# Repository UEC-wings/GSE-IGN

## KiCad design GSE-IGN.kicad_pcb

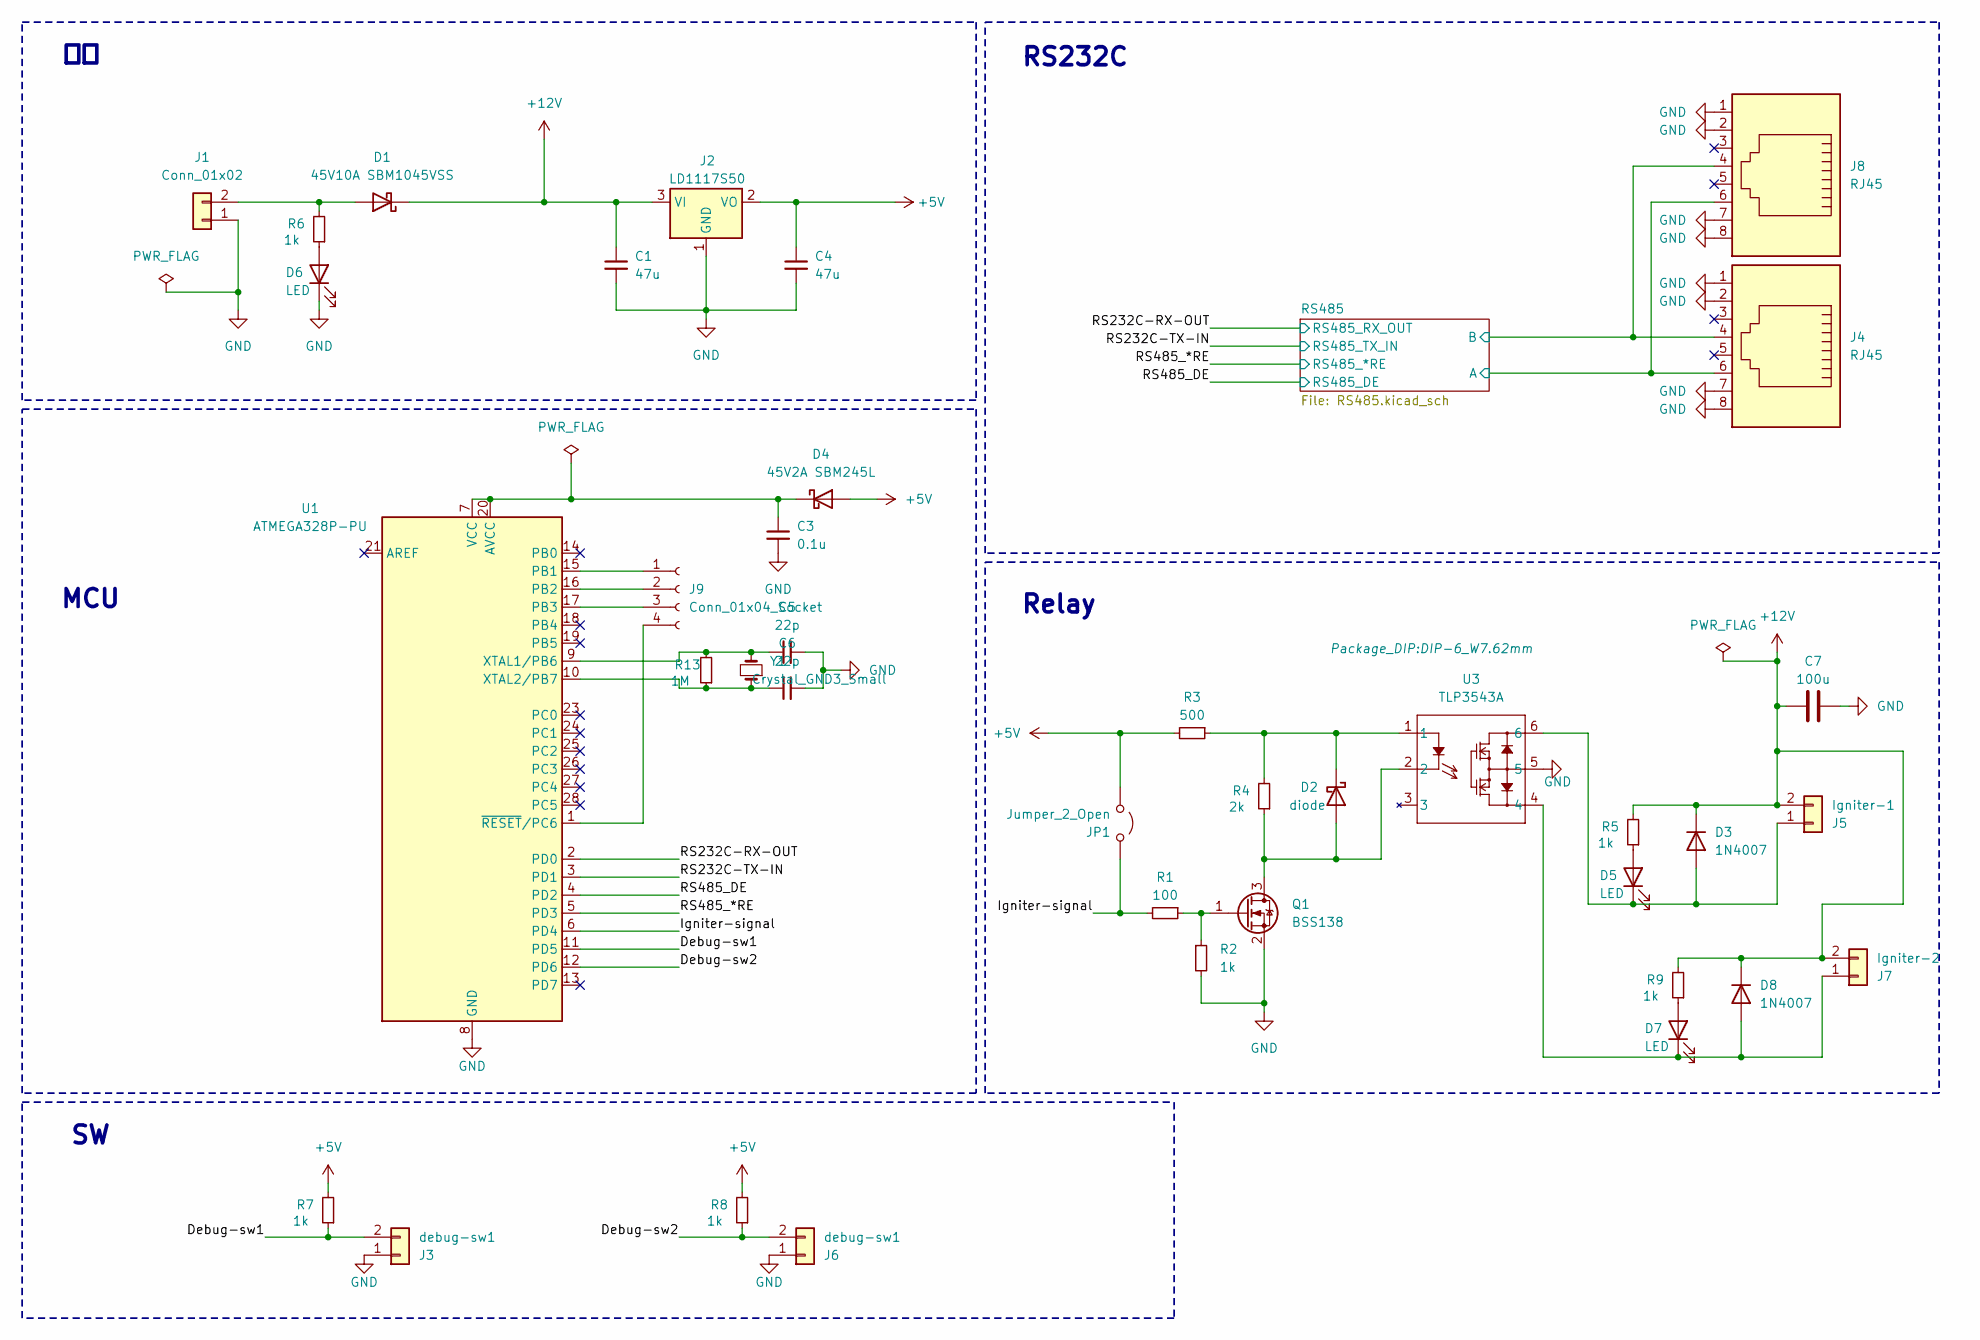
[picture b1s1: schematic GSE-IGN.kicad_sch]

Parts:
C1, C4: 47u; CP_Radial_D4.0mm_P1.50mm
C3: 0.1u; C_0603_1608Metric_Pad1.08x0.95mm_HandSolder
C5, C6: 22p; C_0603_1608Metric
C7: 100u; CP_Radial_D5.0mm_P2.00mm
D1: 45V10A SBM1045VSS; SBM1060LSS_P20mm_Horizontal
D2: diode; D_DO-41_SOD81_P10.16mm_Horizontal
D3, D8: 1N4007; D_DO-41_SOD81_P10.16mm_Horizontal
D4: 45V2A SBM245L; D_DO-41_SOD81_P10.16mm_Horizontal
D5, D6, D7: LED; LED_D3.0mm
J1: Conn_01x02; AMASS_XT60-M_1x02_P7.20mm_Vertical
J2: LD1117S50; SOT-223-3_TabPin2
J3, J6: debug-sw1; JST_XH_B2B-XH-A_1x02_P2.50mm_Vertical
J4, J8: RJ45; 78108P8C
J5: Igniter-1; AMASS_XT60-M_1x02_P7.20mm_Vertical
J7: Igniter-2; AMASS_XT60-M_1x02_P7.20mm_Vertical
J9: Conn_01x04_Socket; PinSocket_1x04_P2.54mm_Vertical
JP1: Jumper_2_Open; JST_XH_B2B-XH-A_1x02_P2.50mm_Vertical
Q1: BSS138; SOT-23
R1: 100; R_Axial_DIN0207_L6.3mm_D2.5mm_P7.62mm_Horizontal
R2, R5, R6, R7, R8, R9: 1k; R_Axial_DIN0207_L6.3mm_D2.5mm_P7.62mm_Horizontal
R3: 500; R_Axial_DIN0207_L6.3mm_D2.5mm_P7.62mm_Horizontal
R4: 2k; R_Axial_DIN0207_L6.3mm_D2.5mm_P7.62mm_Horizontal
R13: 1M; R_Axial_DIN0207_L6.3mm_D2.5mm_P7.62mm_Horizontal
U1: ATMEGA328P-PU; DIP-28_W7.62mm
U3: TLP3543A; DIP-6_W7.62mm
Y1: Crystal_GND3_Small; Crystal_HC49-4H_Vertical

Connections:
+5V: C4.1, D4.2 (A), J2.2 (VO), JP1.1 (A), R3.2, R7.2, R8.2; also elsewhere on the board
+12V: C1.1, C7.1, D1.1 (K), D3.1 (K), D8.1 (K), J2.3 (VI), J5.2, J7.2, R5.2, R9.2
/Debug-sw1: J3.2, R7.1, U1.11 (PD5)
/Debug-sw2: J6.2, R8.1, U1.12 (PD6)
/Igniter-signal: JP1.2 (B), R1.2, U1.6 (PD4)
/RS232C-RX-OUT: U1.2 (PD0); also elsewhere on the board
/RS232C-TX-IN: U1.3 (PD1); also elsewhere on the board
/RS485/A: J4.6, J8.6; also elsewhere on the board
/RS485/B: J4.4, J8.4; also elsewhere on the board
/RS485_*RE: U1.5 (PD3); also elsewhere on the board
/RS485_DE: U1.4 (PD2); also elsewhere on the board
GND: C1.2, C3.2, C4.2, C5.2, C6.2, C7.2, D6.1 (K), J1.1, J2.1 (GND), J3.1, J4.1, J4.2, J4.7, J4.8, J6.1, J8.1, J8.2, J8.7, J8.8, J8.9, J8.10, Q1.2 (S), R2.2, U1.8 (GND), U1.22 (GND), U3.5; also elsewhere on the board
unnamed: D1.2 (A), J1.2, R6.2
unnamed: D2.2 (A), Q1.3 (D), R4.1, U3.2
unnamed: D2.1 (K), R3.1, R4.2, U3.1
unnamed: D3.2 (A), D5.1 (K), J5.1, U3.6
unnamed: C3.1, D4.1 (K), U1.7 (VCC), U1.20 (AVCC)
unnamed: D5.2 (A), R5.1
unnamed: D6.2 (A), R6.1
unnamed: D7.2 (A), R9.1
unnamed: D7.1 (K), D8.2 (A), J7.1, U3.4
unnamed: J9.1, U1.15 (PB1)
unnamed: J9.2, U1.16 (PB2)
unnamed: J9.3, U1.17 (PB3)
unnamed: J9.4, U1.1 (~RESET/PC6)
unnamed: Q1.1 (G), R1.1, R2.1
unnamed: C5.1, R13.2, U1.9 (XTAL1/PB6), Y1.2
unnamed: C6.1, R13.1, U1.10 (XTAL2/PB7), Y1.1

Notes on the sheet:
MCU
Relay
RS232C

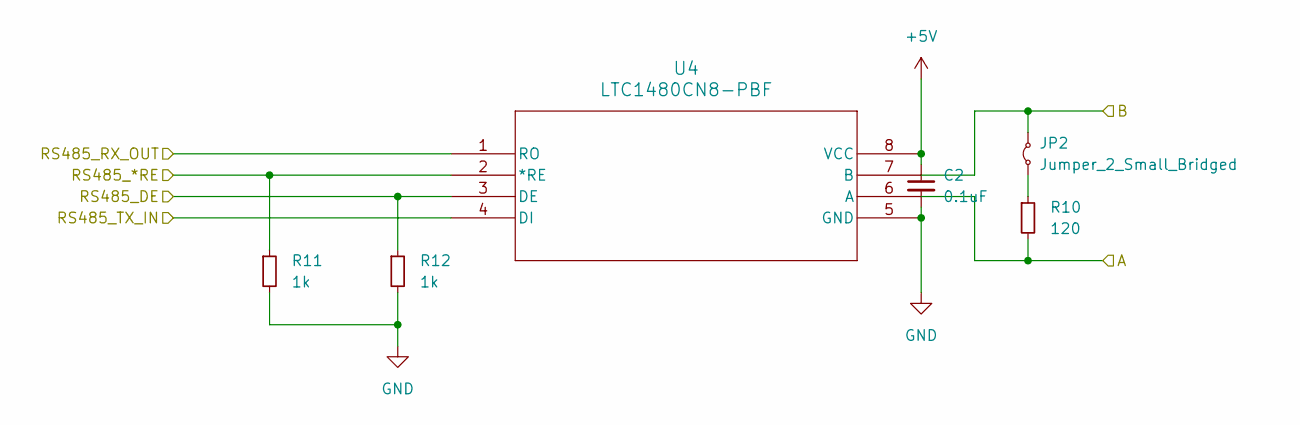
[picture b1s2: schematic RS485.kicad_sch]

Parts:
C2: 0.1uF; C_0603_1608Metric_Pad1.08x0.95mm_HandSolder
JP2: Jumper_2_Small_Bridged; JST_XH_B2B-XH-A_1x02_P2.50mm_Vertical
R10: 120; R_Axial_DIN0207_L6.3mm_D2.5mm_P7.62mm_Horizontal
R11, R12: 1k; R_Axial_DIN0207_L6.3mm_D2.5mm_P7.62mm_Horizontal
U4: LTC1480CN8-PBF; PDIP-8_N_LIT

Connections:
+5V: C2.1, U4.8 (VCC); also elsewhere on the board
/RS232C-RX-OUT: U4.1 (RO); also elsewhere on the board
/RS232C-TX-IN: U4.4 (DI); also elsewhere on the board
/RS485/A: R10.2, U4.6 (A); also elsewhere on the board
/RS485/B: JP2.2 (B), U4.7 (B); also elsewhere on the board
/RS485_*RE: R11.1, U4.2 (*RE); also elsewhere on the board
/RS485_DE: R12.1, U4.3 (DE); also elsewhere on the board
GND: C2.2, R11.2, R12.2, U4.5 (GND); also elsewhere on the board
unnamed: JP2.1 (A), R10.1

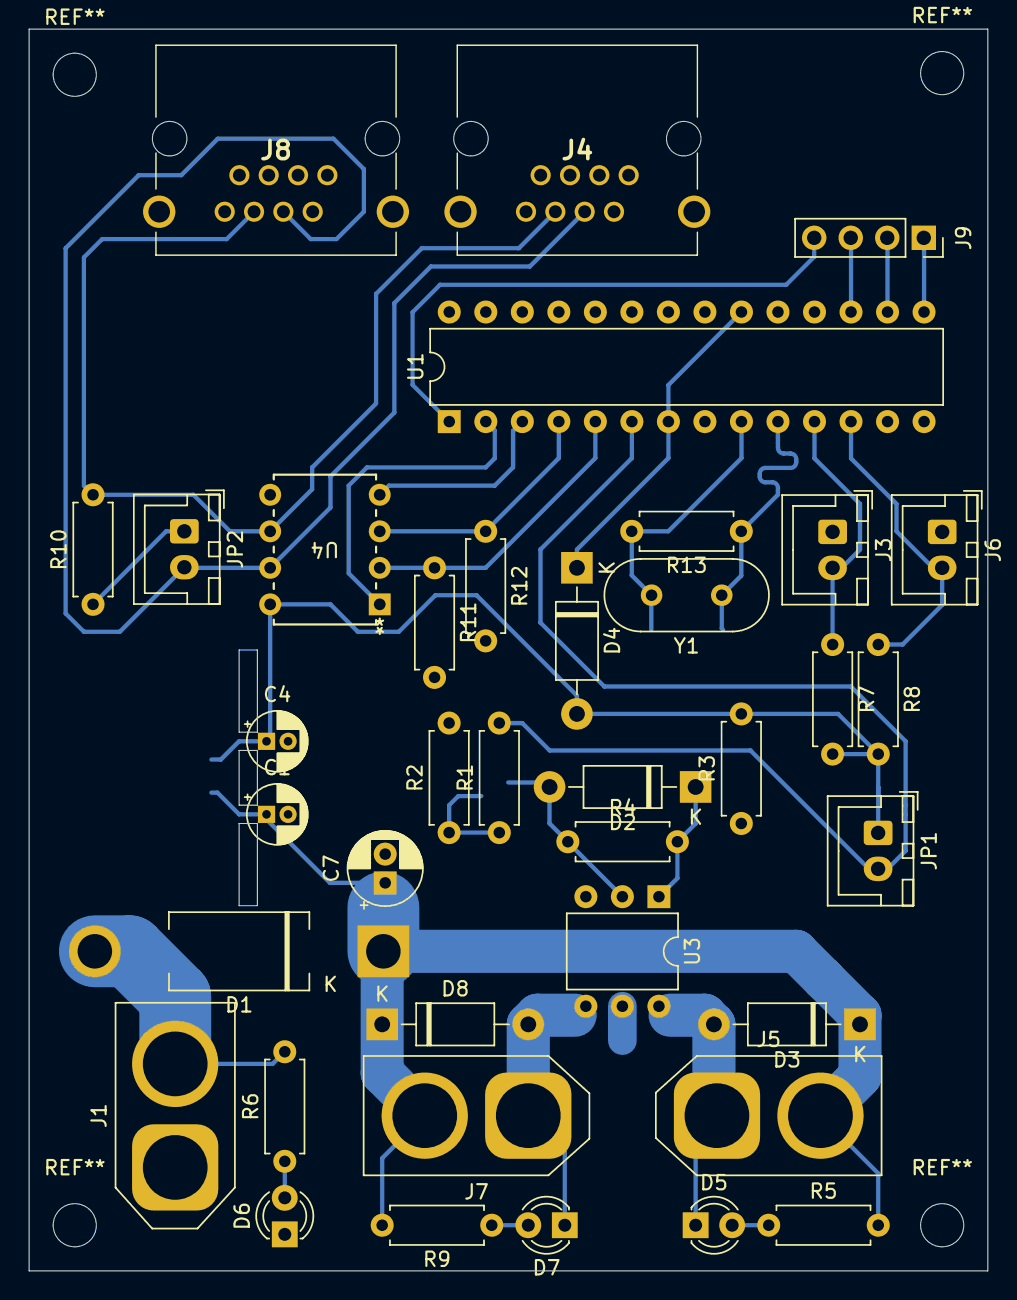
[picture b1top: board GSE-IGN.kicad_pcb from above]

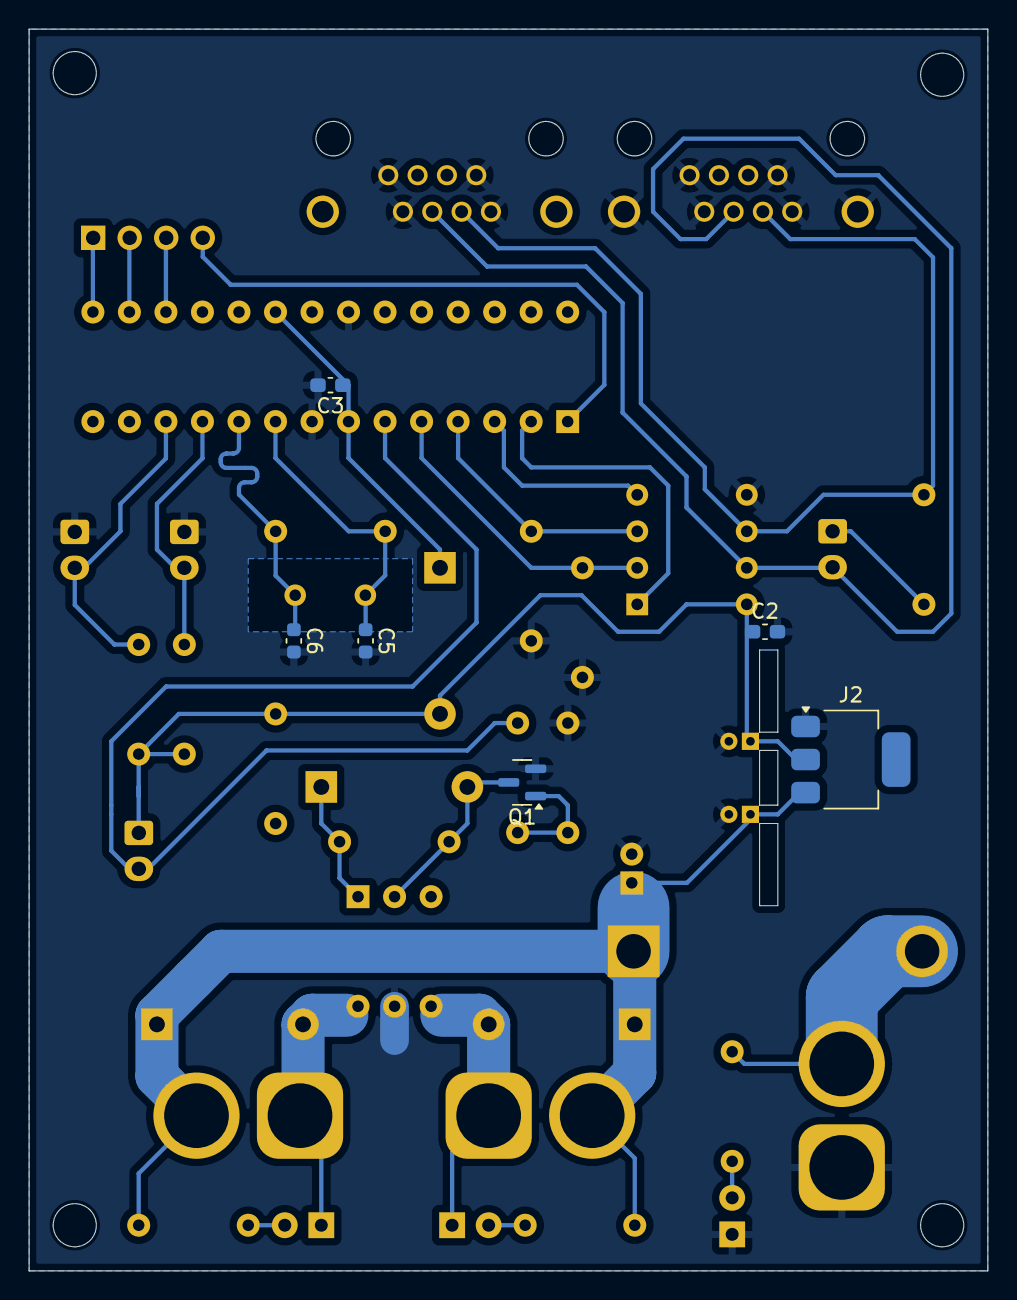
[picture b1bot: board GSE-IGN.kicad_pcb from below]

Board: 2 copper layers, 66.7 x 86.4 mm, 44 parts (6 on the bottom side), 29 nets.

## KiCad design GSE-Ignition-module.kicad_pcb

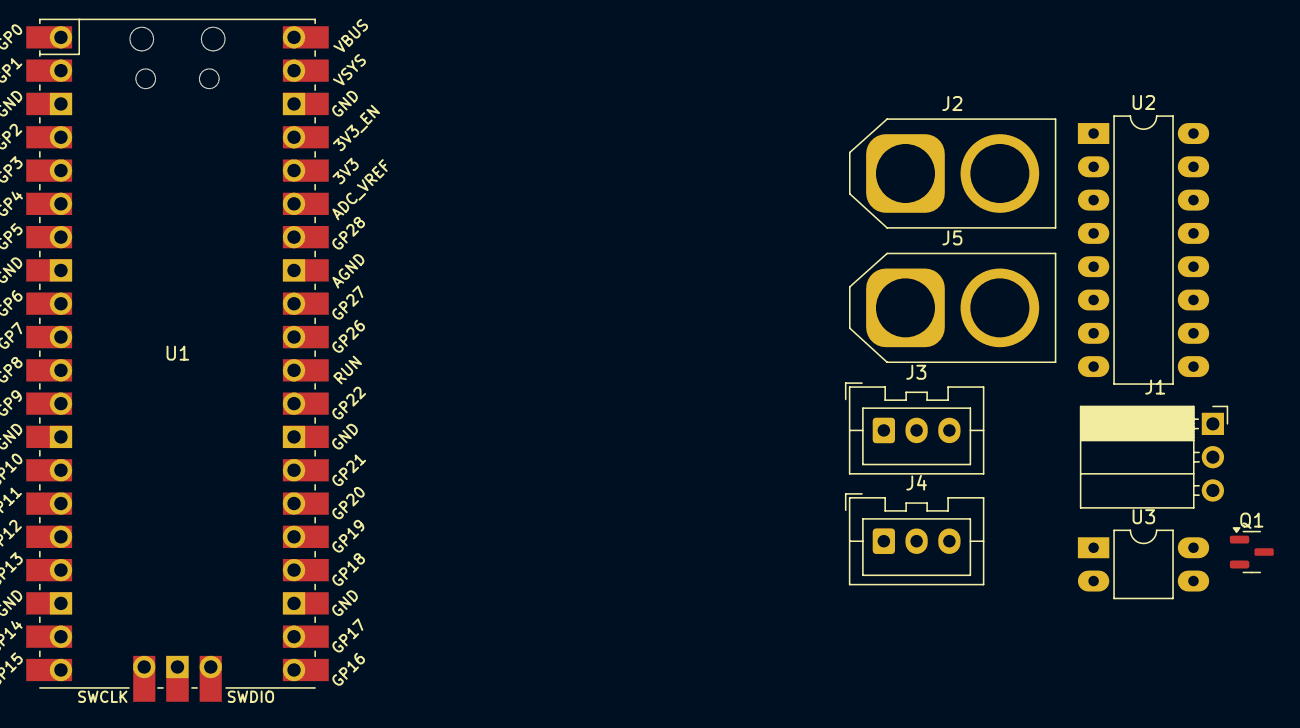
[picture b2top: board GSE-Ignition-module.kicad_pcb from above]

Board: 2 copper layers, 9 parts (0 on the bottom side), 11 nets, no tracks yet.

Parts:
J1: DCDC-Regulator-12Vto3.3V; PinSocket_1x03_P2.54mm_Horizontal
J2: Conn_01x02; AMASS_XT60-M_1x02_P7.20mm_Vertical
J3: RS232C-1; JST_XA_B03B-XASK-1_1x03_P2.50mm_Vertical
J4: RS232C-2; JST_XA_B03B-XASK-1_1x03_P2.50mm_Vertical
J5: Igniter-1; AMASS_XT60-F_1x02_P7.20mm_Vertical
Q1: BSS138; SOT-23
U1: Pico; RPi_Pico_SMD_TH
U2: ADM3202ANZ; DIP-16_W7.62mm_LongPads
U3: TLP241A; DIP-4_W7.62mm_LongPads

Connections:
+3.3V: J1.1, U1.39 (VSYS), U2.16 (VCC)
GND: J1.2, J2.1, J3.2, J4.2, J5.2, Q1.2 (S), U1.3 (GND), U1.38 (GND), U2.15 (GND)
unnamed: Q1.3 (D), U3.2
unnamed: J5.1, U3.3
RS232C-RX1-IN: J3.3, U2.13 (R1IN)
RS232C-RX1-OUT: U1.2 (GPIO1), U2.12 (R1OUT)
RS232C-RX2-IN: J4.3, U2.8 (R2IN)
RS232C-TX1-IN: U1.1 (GPIO0), U2.11 (T1IN)
RS232C-TX1-OUT: J3.1, U2.14 (T1OUT)
RS232C-TX2-OUT: J4.1, U2.7 (T2OUT)
VCC: J1.3, U3.4

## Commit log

2024-09-19 Create main.yaml
    add generate-kicad-files Github Action
2024-09-19 Add .gitignore file to ignore GSE-Ignition-module-backups and fp-info-cache
2024-09-19 Refactor GitHub Actions workflow file
2024-12-10 Rename GSE-Ignition-module files and update .gitignore; add new fp-info-cache file
2025-03-31 色々変更
2025-05-11 schはたぶん完成
2025-05-24 部品を配置
2025-05-30 アートワーク終わり
2025-06-04 少し小型化
